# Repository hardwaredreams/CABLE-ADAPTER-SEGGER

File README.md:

# SEGGER J-LINK用ケーブルアダプタ

この基板は、SEGGER Microcontroller (以降 SEGGER と略記)社製 デバッグプローブ J-LINKの接続ケーブルの変換アダプタ基板です。
(非純正品。ケーブル類は付属しません。SEGGER社等 メーカー・商社等からのサポートはありません)

 J-LINKからターゲット基板に接続するためのコネクタおよびケーブルは、0.1インチ、20ピンのケーブルが使用されています。
 ターゲット基板に ハーフピッチの 10ピンコネクタが実装、または 10ピンニードルアダプタ用パッドが使用されている場合に、
 ターゲットに合わせたケーブルに変換して使用できるようにすることを目的としたものです。
 ターゲット基板にあわせて、どちらかにケーブルを接続してください。
J-LINKでのピン配置情報を元に設計していますが、 ARMマイコン用の JTAG/SWD プローブは、どの製品も基本的に同じピン配列になっています。
SEGGER社製 J-LINK以外でも使えるはずですが、確認はしていません。

## 構成
この基板は、J-LINK と 用途に応じてターゲット基板へ接続するために 3つのコネクタが実装されています。 ケーブル類は、付属しませんので、ユーザ側で準備する必要があります。

* 20-Pinコネクタ
    * J-LINKへ接続する 20ピンフラットケーブルを接続するためのコネクタです
* 10-Pinコネクタ (0.1インチピッチ)
    * ターゲットへ接続する 10-Pin Needle Adapter のケーブルを接続するためのコネクタです。
    ピンアサインや、ターゲット基板上のフットプリントについては SEGGER 社の 10-Pin Needle Adapter のページなどを参照してください。

* 10-Pinコネクタ (0.05インチ、ハーフピッチ)
    * ターゲットへ接続する ハーフビッチの 10ピンフラットケーブルを接続するためのコネクタです (7番ピンがキーピンにして 9ピン構成になっている場合が多い)

## 使用ケーブルについて
必要に応じて、ユーザ側でご用意、使用してください

* 20-Pin ケーブル
    * J-LINKと接続するためのケーブルです。1.27mmピッチで 20ピンのストレートケーブルです。 J-LINK等に付属しています。

* 10-Pin Needle Adapger ケーブル
    * ターゲット基板上に、設けられたコンタクト用パッドに スプリングタイプのコンタクトを使用して接続するタイプのケーブルです。 SEGGER J-LINK用ケーブルアダプタ側は、1.27mmピッチで 10ピンのコネクタが使用されています。

* 10-Pin ハーフピッチケーブル
    * ターゲット基板上に設けられた ハーフピッチ 10-Pinコネクタと接続するための 0.635mmmピッチ ケーブルです。ターゲット基板側コネクタの 7番ピンが逆挿し防止用に欠いてある場合があります。ケーブルは、これに対応して 7番ピンの位置にキーピンが挿入されている場合があります。この場合、キーピンを抜き、挿入方向に注意して使用してください。

## 使用方法
20ピンコネクタ側をフラットケーブルを使って J-LINKと接続します。
ターゲット基板とは 10pin Needle Adapter または 10pin ハーフピッチコネクタの いずれか一方、適合する側を利用して接続します。

注意: この基板の10ピン ハーフピッチコネクタには 7番ピンがあります。 フラットケーブルコネクタの 7番ピンにキーピンがある場合、挿入できませんから、キーピンを抜いてから使用してください。挿入する際に、ケーブルの向きに注意してください。コネクタの 1番ピン側に ▲マークがあります。通常ケーブルの 1番ピン側に色付きのマーカーがあります。

10pin Needle Adapter と 10pinハーフピッチは、ピン配置に互換性がありませんので、注意してください。

## 接続使用例

     ハーフピッチコネクタ 使用時

    Tag Connect 使用時

    写真で使用している j-link との接続用 20ピンケーブルは、非純正品です。

## 回路図

[回路図](documents/CABLE-ADAPTER-SEGGER.pdf)

## 部品
この基板に使用している部品の参考情報です。但し、この基板には、スペック的に同等になる廉価版を使用しています。

|ID|型番|品名|メーカー | 摘要|
|---|---|---|---|---|
|CN1| HIF3F-20PA-2.54DSA(71) |20ピン ボックス ピンヘッダ | ヒロセ電機 ||
|CN2| HPH2-A-10-UA-SMT |ハーフピッチ 10ピンヘッダ  | Adam Tech |SMDタイプ|
|CN3| HIF3F-10PA-2.54DSA(71) |10ピン ボックス ピンヘッダ | ヒロセ電機 ||

## Q&A

    (今後 追加予定)

## 参考
* [SEGGER社 J-LINKシリーズ ](https://www.segger.com/products/debug-probes/j-link/)
    * [9-Pin Cortex-M Adapter](https://www.segger.com/products/debug-probes/j-link/accessories/adapters/9-pin-cortex-m-adapter/)
    * [10-Pin Needle Adapter](https://www.segger.com/products/debug-probes/j-link/accessories/adapters/10-pin-needle-adapter/)

    SEGGER社の 9-Pin Cortex-M Adapter や 10-Pin Needle Adaper には J-LINK接続用のアダプタ基板も付属います。

* Olimex社製 JTAG 20pin-10pin アダプタ
    * [ARM-JTAG-20-10](https://www.olimex.com/Products/ARM/JTAG/ARM-JTAG-20-10/)

    Olimex社製は、20pin ケーブルを使用せずに、基板を直接 デバッグプローブに接続でき、10pin ハーフピッチケーブルが付属するようです。

* 20pin ケーブル
    * [2×10(20P)両端コネクター付IDCリボンケーブル(フラットケーブル)](https://akizukidenshi.com/catalog/g/g113378/) (秋月電子通商)

    J-LINK 添付品の相当品
    
* 10pin ハーフピッチケーブル
    * [2×5(10P)両端コネクター付IDCリボンケーブル(フラットケーブル ハーフピッチ)](https://akizukidenshi.com/catalog/g/g106776/) (秋月電子通商)

* 10pin ニードルコンタクトケーブル (Tag Connect 製)
    * [TC2050-IDC – Tag-Connect 2050 IDC](https://www.tag-connect.com/product/tc2050-idc-tag-connect-2050-idc)
    * [TC2050-IDC-NL 10-Pin No-Legs Cable with Ribbon connector](https://www.tag-connect.com/product/tc2050-idc-nl-10-pin-no-legs-cable-with-ribbon-connector)
    * [TC2050-CLIP-3PACK Retaining CLIP board for TC2050-NL cables - 3 Pack](https://www.tag-connect.com/product/tc2050-clip-3pack-retaining-clip)

    ニードルコンタクトを使用される場合は、リテーナをあわせて使用することができます

## 基板外観図

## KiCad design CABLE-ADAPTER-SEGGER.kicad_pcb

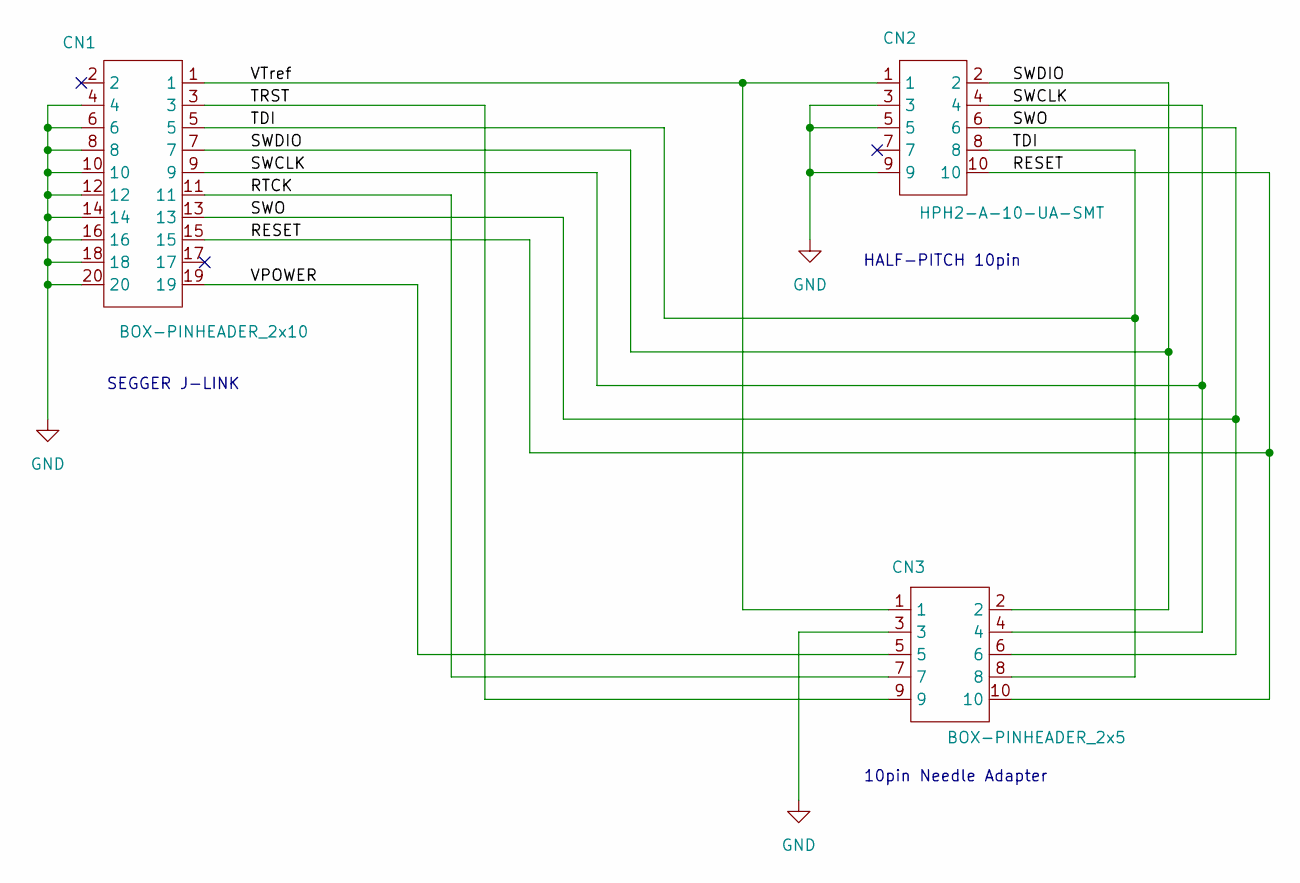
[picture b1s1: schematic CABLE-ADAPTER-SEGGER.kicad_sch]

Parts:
CN1: BOX-PINHEADER_2x10; MIL-BOX-PINHEADER_2x10
CN2: HPH2-A-10-UA-SMT
CN3: BOX-PINHEADER_2x5; mil-box-pinheader_2x5

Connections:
/RESET: CN1.15, CN2.10, CN3.10
/RTCK: CN1.11, CN3.7
/SWCLK: CN1.9, CN2.4, CN3.4
/SWDIO: CN1.7, CN2.2, CN3.2
/SWO: CN1.13, CN2.6, CN3.6
/TDI: CN1.5, CN2.8, CN3.8
/TRST: CN1.3, CN3.9
/VPOWER: CN1.19, CN3.5
/VTref: CN1.1, CN2.1, CN3.1
GND: CN1.4, CN1.6, CN1.8, CN1.10, CN1.12, CN1.14, CN1.16, CN1.18, CN1.20, CN2.3, CN2.5, CN2.9, CN3.3

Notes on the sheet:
10pin Needle Adapter
HALF-PITCH 10pin
SEGGER J-LINK

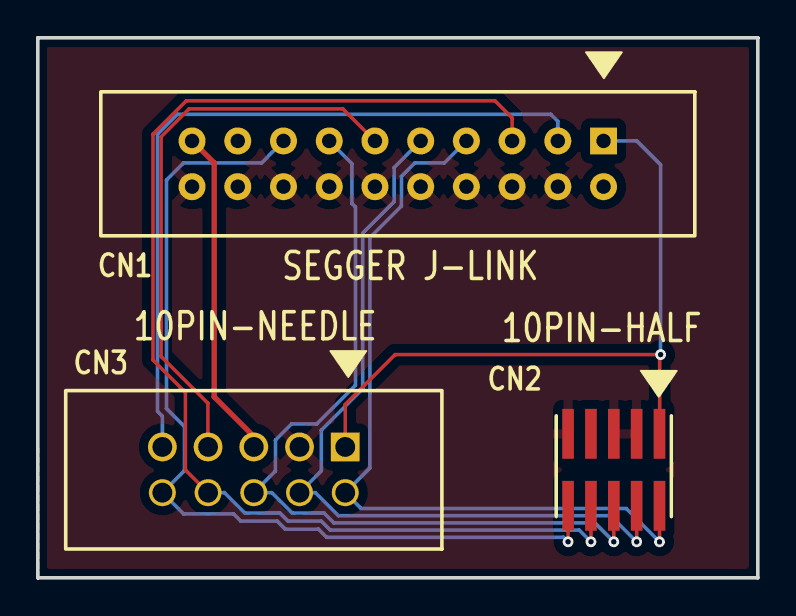
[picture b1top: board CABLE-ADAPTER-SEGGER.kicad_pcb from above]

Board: 2 copper layers, 40.0 x 30.0 mm, 3 parts (0 on the bottom side), 10 nets.

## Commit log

2025-02-20 1st commit
2025-02-28 1st commit やりなおし
2025-02-28 CN2とCN3の記載が逆だったのを修正
2025-03-05 使用時の写真を追加
2025-03-05 一部、記述追加。 写真追加対応
